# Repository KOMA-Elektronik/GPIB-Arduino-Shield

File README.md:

# **GPIB ARDUINO SHIELD**

This repo contains a little set of tools to talk to old digital multimeters (DMM) via GPIB.

### You'll need:
* Arduino Uno R3
* GPIB Shield from this repo (production files available)
* GPIB capable DMM
* GPIB cable
* PC with Python 3 installed and USB cable
* `serial` library for Python

### How to set it up:

* connect an Arduino Uno R3 over USB to the computer
* attach the GPIB Shield with a GPIB cable connected to the DMM
* run the Python script

# GPIB Connection
The very old (and very bad) standard [IEEE-488](https://en.wikipedia.org/wiki/IEEE-488) is available on the back of a lot of older DMMs. With the help of an Arduino Uno R3 board, the 8-bit parallel bus can be converted to a serial connection and send over to the host PC via USB. 

# Contribution
If you find this repository useful and implemented a connection to a DMM that has not yet been added to the `Devices` folder - we would love to add it!

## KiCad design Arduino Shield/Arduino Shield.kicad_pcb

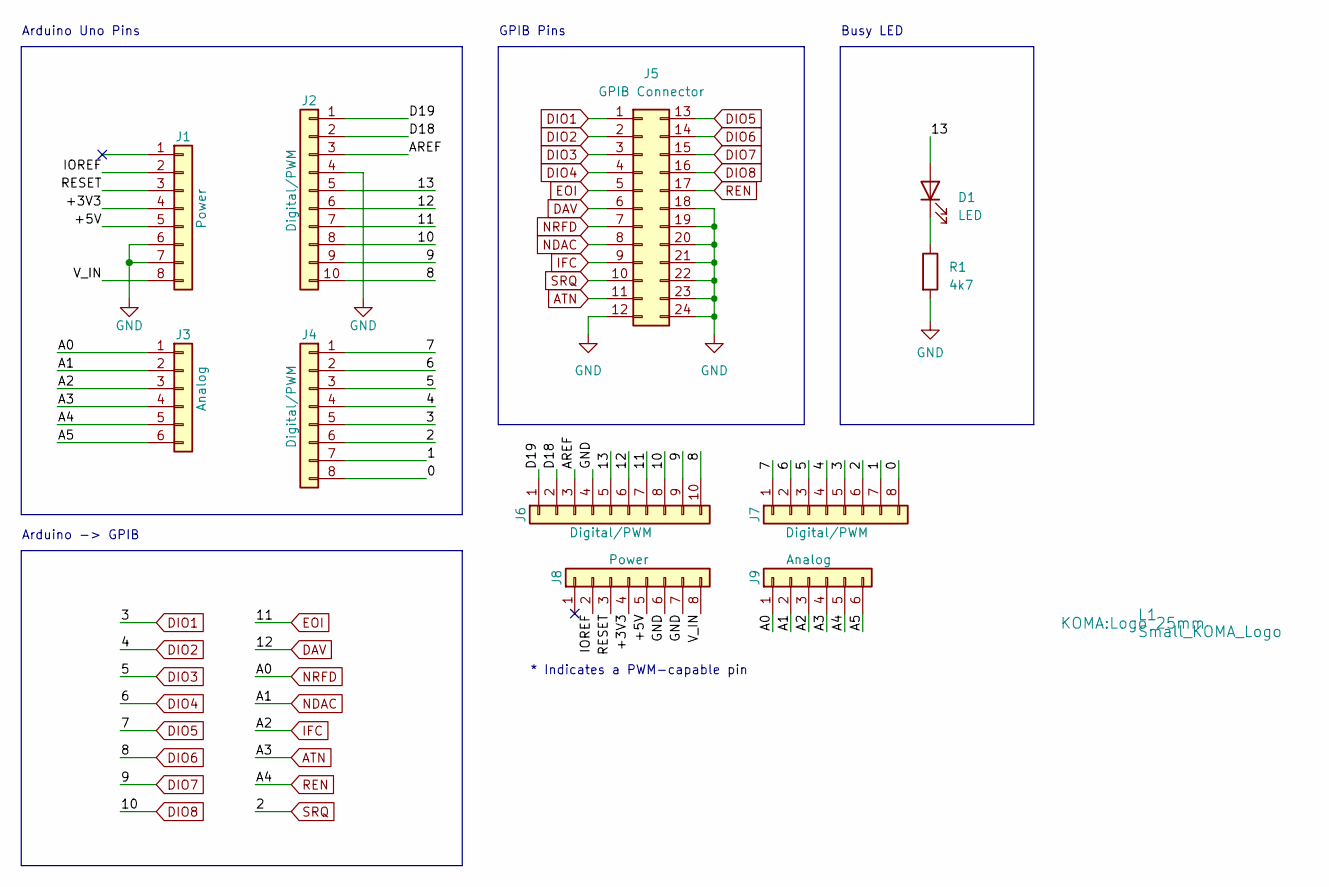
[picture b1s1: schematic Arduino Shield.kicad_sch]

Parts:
D1: LED; LED_D3.0mm
J1, J8: Power; PinHeader_1x08_P2.54mm_Vertical
J2, J6: Digital/PWM; PinHeader_1x10_P2.54mm_Vertical
J3, J9: Analog; PinHeader_1x06_P2.54mm_Vertical
J4, J7: Digital/PWM; PinHeader_1x08_P2.54mm_Vertical
J5: GPIB Connector; NorComp 24 Pins female vertical dip solder
L1: Small_KOMA_Logo; Logo 25mm
R1: 4k7; R_Axial_DIN0207_L6.3mm_D2.5mm_P7.62mm_Horizontal

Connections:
/0: J4.8, J7.8
/1: J4.7, J7.7
/13: D1.2 (A), J2.5, J6.5
/+3V3: J1.4, J8.4
/+5V: J1.5, J8.5
/A5: J3.6, J9.6
/AREF: J2.3, J6.3
/D18: J2.2, J6.2
/D19: J2.1, J6.1
/IOREF: J1.2, J8.2
/RESET: J1.3, J8.3
/V_IN: J1.8, J8.8
ATN: J3.4, J5.11, J9.4
DAV: J2.6, J5.6, J6.6
DIO1: J4.5, J5.1, J7.5
DIO2: J4.4, J5.2, J7.4
DIO3: J4.3, J5.3, J7.3
DIO4: J4.2, J5.4, J7.2
DIO5: J4.1, J5.13, J7.1
DIO6: J2.10, J5.14, J6.10
DIO7: J2.9, J5.15, J6.9
DIO8: J2.8, J5.16, J6.8
EOI: J2.7, J5.5, J6.7
GND: J1.6, J1.7, J2.4, J5.12, J5.18, J5.19, J5.20, J5.21, J5.22, J5.23, J5.24, J6.4, J8.6, J8.7, R1.2
IFC: J3.3, J5.9, J9.3
NDAC: J3.2, J5.8, J9.2
NRFD: J3.1, J5.7, J9.1
unnamed: D1.1 (K), R1.1
REN: J3.5, J5.17, J9.5
SRQ: J4.6, J5.10, J7.6

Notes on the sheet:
GPIB Pins
Arduino -> GPIB
Busy LED
* Indicates a PWM-capable pin
Arduino Uno Pins

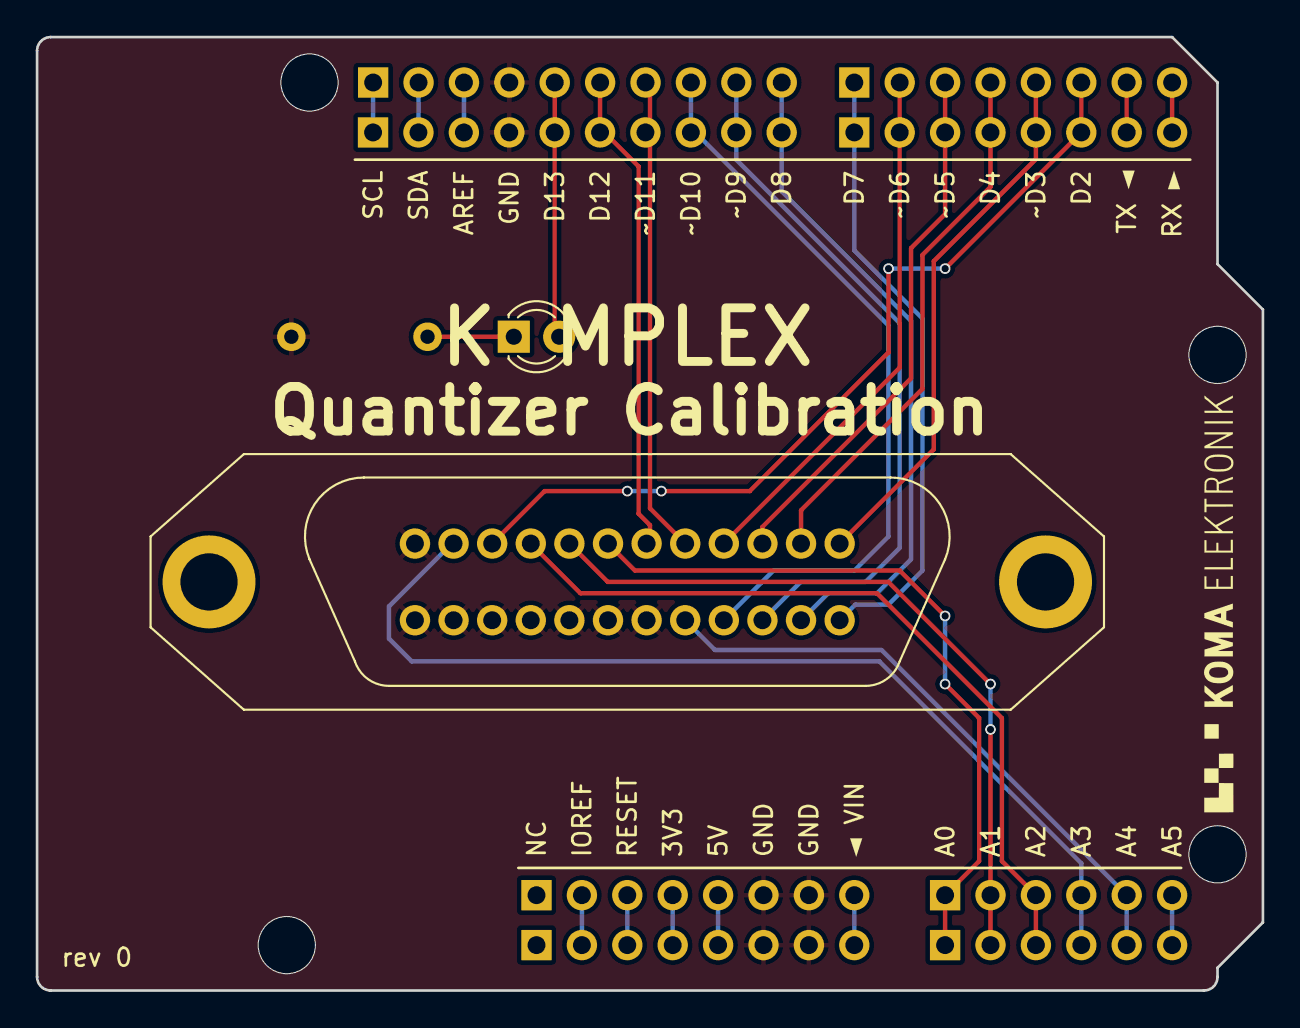
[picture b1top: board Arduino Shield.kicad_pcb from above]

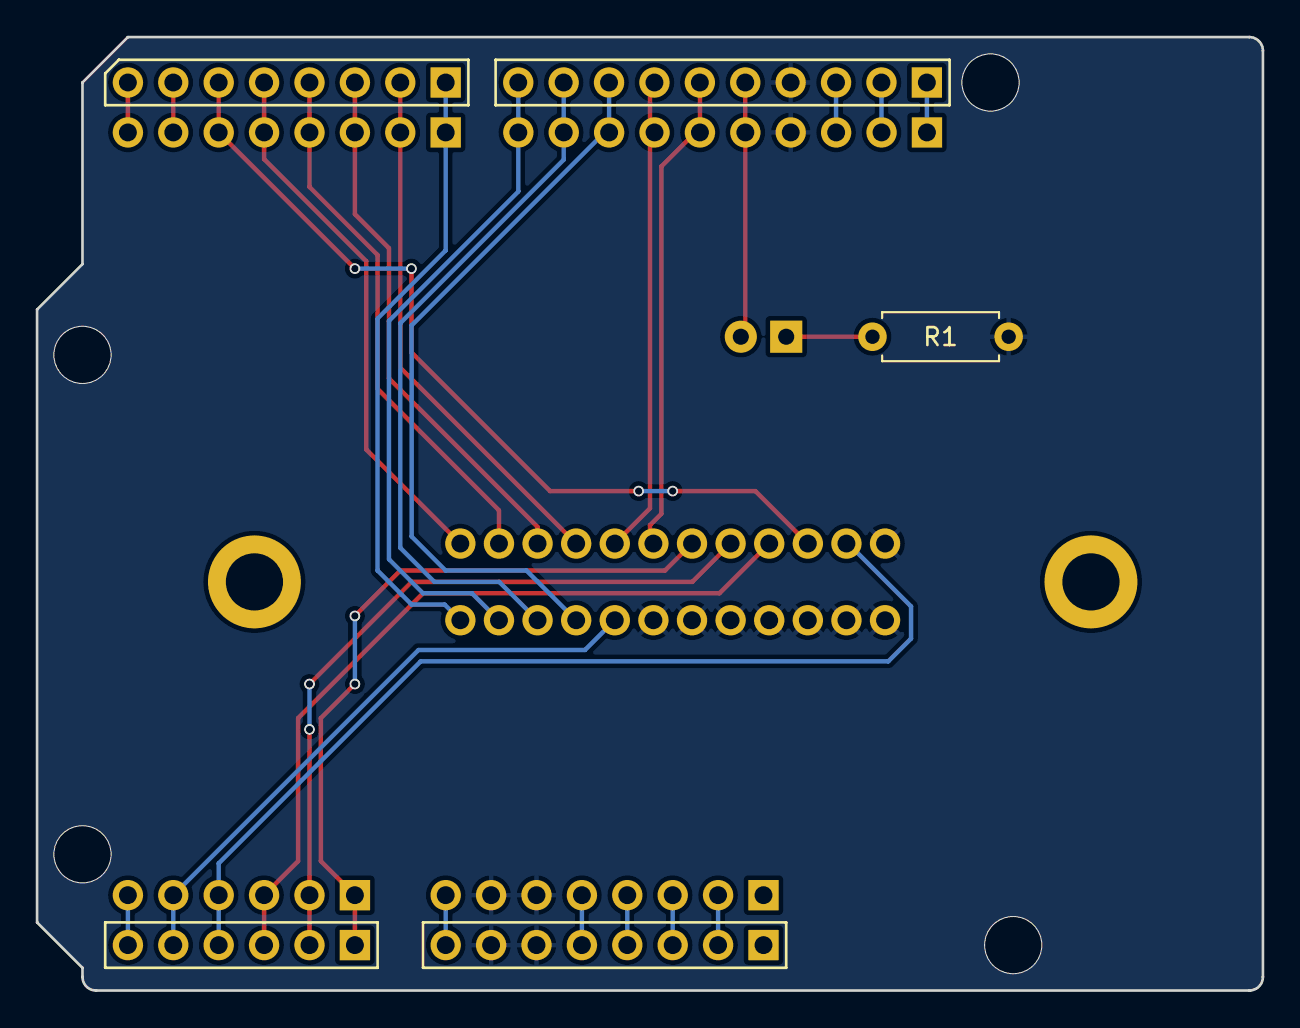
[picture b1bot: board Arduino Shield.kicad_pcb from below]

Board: 2 copper layers, 68.6 x 53.3 mm, 16 parts (5 on the bottom side), 30 nets.

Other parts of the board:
MH1, MH2, MH3, MH4: MountingHole_3.2mm

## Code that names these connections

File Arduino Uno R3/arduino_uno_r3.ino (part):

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 */

/* configurable pin mapping to Arduino Micro */
#define DIO1  3  /* GPIB 1  : I/O data bit 1 */
#define DIO2  4  /* GPIB 2  : I/O data bit 2 */
#define DIO3  5  /* GPIB 3  : I/O data bit 3 */
#define DIO4  6  /* GPIB 4  : I/O data bit 4 */
#define DIO5  7  /* GPIB 13 : I/O data bit 5 */
#define DIO6  8  /* GPIB 14 : I/O data bit 6 */
#define DIO7  9  /* GPIB 15 : I/O data bit 7 */
#define DIO8  10  /* GPIB 16 : I/O data bit 8 */
#define EOI   11  /* GPIB 5  : End Or Identify */
#define DAV   12  /* GPIB 6  : Data Valid */
#define NRFD  A0  /* GPIB 7  : Not Ready For Data */
#define NDAC  A1  /* GPIB 8  : Not Data Accepted */
#define IFC   A2  /* GPIB 9  : Interface Clear */
#define ATN   A3  /* GPIB 11 : Attention */
#define REN   A4  /* GPIB 17 : Remote Enable */
#define SRQ    2  /* GPIB 10 : Service Request
                     This Arduino pin must have interrupt */
#define SRQ_i  2  /* Interrupt number for the SRQ pin (see Arduino doc) */
#define LED   13  /* Busy signal (board is waiting), 13 is the on-board LED */

/* serial commands */
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/* engage/disengage SRQ interruption */
void int_set_srq(boolean state) {
  int_srq_engaged = state;
  pinMode(SRQ, INPUT_PULLUP);
  if (state) {
    attachInterrupt(SRQ_i, _int_cb_srq, LOW);
  } else {
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
/* reset GPIB data lines to HiZ */
void pio_reset() {
  pinMode(DIO1, INPUT_PULLUP);
  pinMode(DIO2, INPUT_PULLUP);
  pinMode(DIO3, INPUT_PULLUP);
  pinMode(DIO4, INPUT_PULLUP);
  pinMode(DIO5, INPUT_PULLUP);
  pinMode(DIO6, INPUT_PULLUP);
  pinMode(DIO7, INPUT_PULLUP);
  pinMode(DIO8, INPUT_PULLUP);
}

/* get byte from GPIB data lines */
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
/* set byte on GPIB data lines */
void pio_write(byte b) {
  pinMode(DIO1, OUTPUT); digitalWrite(DIO1, bitRead(~b, 0));
  pinMode(DIO2, OUTPUT); digitalWrite(DIO2, bitRead(~b, 1));
  pinMode(DIO3, OUTPUT); digitalWrite(DIO3, bitRead(~b, 2));
  pinMode(DIO4, OUTPUT); digitalWrite(DIO4, bitRead(~b, 3));
  pinMode(DIO5, OUTPUT); digitalWrite(DIO5, bitRead(~b, 4));
  pinMode(DIO6, OUTPUT); digitalWrite(DIO6, bitRead(~b, 5));
  pinMode(DIO7, OUTPUT); digitalWrite(DIO7, bitRead(~b, 6));
  pinMode(DIO8, OUTPUT); digitalWrite(DIO8, bitRead(~b, 7));
}

/* send GPIB bus state back to computer */
void gpib_status() {
  Serial.write(OUT_STRING);
  pinMode(EOI, INPUT_PULLUP); Serial.print("E"); Serial.print(digitalRead(EOI));
  pinMode(DAV, INPUT_PULLUP); Serial.print("D"); Serial.print(digitalRead(DAV));
  pinMode(NRFD,INPUT_PULLUP); Serial.print("N"); Serial.print(digitalRead(NRFD));
  pinMode(NDAC,INPUT_PULLUP); Serial.print("n"); Serial.print(digitalRead(NDAC));
  pinMode(IFC, INPUT_PULLUP); Serial.print("I"); Serial.print(digitalRead(IFC));
  pinMode(SRQ, INPUT_PULLUP); Serial.print("S"); Serial.print(digitalRead(SRQ));
  pinMode(ATN, INPUT_PULLUP); Serial.print("A"); Serial.print(digitalRead(ATN));
  pinMode(REN, INPUT_PULLUP); Serial.print("R"); Serial.print(digitalRead(REN));
  pio_reset();
  Serial.print(digitalRead(DIO8));
  Serial.print(digitalRead(DIO7));
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

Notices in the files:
Arduino Uno R3/arduino_uno_r3.ino:
Copyright 2013 Thibault VINCENT <tibal@reloaded.fr>
Agipibi is free software: you can redistribute it and/or modify
it under the terms of the GNU General Public License as published by
the Free Software Foundation, either version 3 of the License, or
(at your option) any later version.
